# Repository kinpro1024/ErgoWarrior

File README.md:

# ErgoWarrior

**ErgoWarrior is a completely open-source, ergonomic hitbox-style leverless controller. It was born out of a complete lack of contoured open-source ergonomic hitbox designs.**

*To the best of my knowledge, this is the **first open-source** Contoured Ergonomic Hitbox on a public platform.*

# Major Update: An overhaul of the Handle/Bridge Design is in the works. (Released as v1.1.0)

**I had the Handle Fail and Break in my flight luggage as it was being thrown around. ErgoWarrior was designed to be robust, and this result was not good enough. The overhaul will also address the inability to completely remove cables once assembled, enhancing repairability.**

**ErgoWarrior v1.1.0 Mechanical Design.**

**ErgoWarrior v1.0.0 Mechanical Design.**

**ErgoWarrior v1.0.0 has a robust handle. (It did not, that has been fixed.)**

**Right Half of ErgoWarrior's Pre-Alpha Build.**

## Why an Ergo-Design Matters

Traditional flat controllers force the wrists and fingers into unnatural positions. Over time, this can lead to discomfort, fatigue, and even injuries such as Repetitive Strain Injury (RSI) or Carpal Tunnel Syndrome.

An ergo-design, **like ErgoWarrior**, is built to keep your hands and wrists in a natural, relaxed posture. This brings several benefits:

- **Reduced Strain and Injury Risk**: Many people (myself included) are highly prone to wrist injuries, ErgoWarrior is designed to keep wrists neutral, lowering stress on muscles and tendons.
- **Better Comfort for Extended Use**: Less fatigue during long sessions.
- **Improved Precision and Performance**: Inputs are always in reach and yet equally intuitive.
- **Natural Hand Posture**: Designed to closely match human anatomy for optimal control and comfort.
- **Advanced Techniques Still Possible**: Techniques like double taps or quick buffering inputs are still very much preserved and possible.

In short, ergonomic designs are not just about comfort, they improve performance and intend to protect your hands over the long term.

### Hardware and Assembly

Raspberry Pi Pico is the main dev-board platform for ErgoWarrior. May change to a custom dev-board in the future.

Cherry MX Low Profile switches are the switches used throughtout all forseen generations of Ergowarrior.

ErgoWarrior is designed to go with [M3 Hex Socket 10mm Screws](https://onlyscrews.in/products/m3-x-10mm-hex-allen-socket-head-high-tensile12-9-black-anodized-screw?_pos=17&_sid=9edb84e19&_ss=r) and [8mm M3 Injection Molding Brass Inserts](https://onlyscrews.in/products/m3-x-8mm-brass-threaded-inserts).

Refer to Instructions.md for full instructions in assembly.

**Print Settings:** All Prints except the ultralight arcade button are done at 0.2mm layer height with the latter at 0.08mm LH. Refer to 3mf files for full details.
**Note:** Some Sanding is required on the jump buttons for optimal fit.

### Firmware

Firmware used for ErgoWarrior is a tweaked build of [GP2040-CE](https://github.com/OpenStickCommunity/GP2040-CE). Plug-and-Play firmware will drop soon. Until then stock GP2040-CE for the Raspberry Pi Pico must be used. Keybinds as below:

## Note on Sizing

The ErgoWarrior is currently available in **only one size**, which corresponds to my personal hand size.  
If you need a different size, you may scale and modify the model yourself with the step files to better fit your requirements.

*If you're unsure how to do that, feel free to open an issue thread in the repository. I’m not making any promises at the moment, but I will look into it if possible.*

## Timeline

### v0.0.0 and v0.5.0 (Alpha and Beta Builds) (Released on 19/Oct/2025) (Deprecated)

A kof style 4+4 (L+R) controller was released as Alpha Build by mid-October ~~with a beta build arriving on the same platform in late October~~. (Alpha Build out.) (Beta build cancelled, changes merged with v1.)

### v1.0.0 (Full Release) (Released on 29/Nov/2025) (Deprecated)

A Third-Strike style controller with a (6+10)* (L+R) layout was slated for release in ~~mid-November~~ late-November (Delay in arrival of PCBs).

### v1.1.0 (Released on 20/Apr/2026)

This was not a a release I had planned, however as the ErgoWarrior handle failed in what I would call abnormal but expected load conditions, I have completely reworked the handle, this time using Topology Optimisation to make it absolutely sure it does not fail like that again.

\* **Tentative, may change.**

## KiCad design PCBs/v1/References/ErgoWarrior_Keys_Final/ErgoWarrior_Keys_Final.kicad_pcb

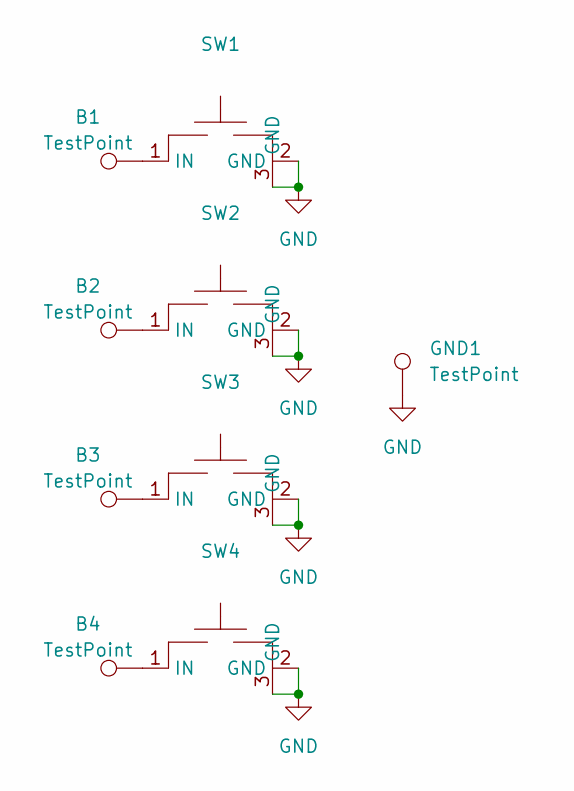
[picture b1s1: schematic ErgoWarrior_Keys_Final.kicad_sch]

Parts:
B1, B2, B3, B4: TestPoint; TestPoint_THTPad_D1.5mm_Drill0.7mm
GND1: TestPoint; TestPoint_THTPad_1.5x1.5mm_Drill0.7mm
SW1, SW2, SW3, SW4: Cherry_MX_LP_Mirrorable

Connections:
GND: GND1.1, SW1.2 (GND), SW1.3 (GND), SW2.2 (GND), SW2.3 (GND), SW3.2 (GND), SW3.3 (GND), SW4.2 (GND), SW4.3 (GND)
unnamed: B1.1, SW1.1 (IN)
unnamed: B2.1, SW2.1 (IN)
unnamed: B3.1, SW3.1 (IN)
unnamed: B4.1, SW4.1 (IN)

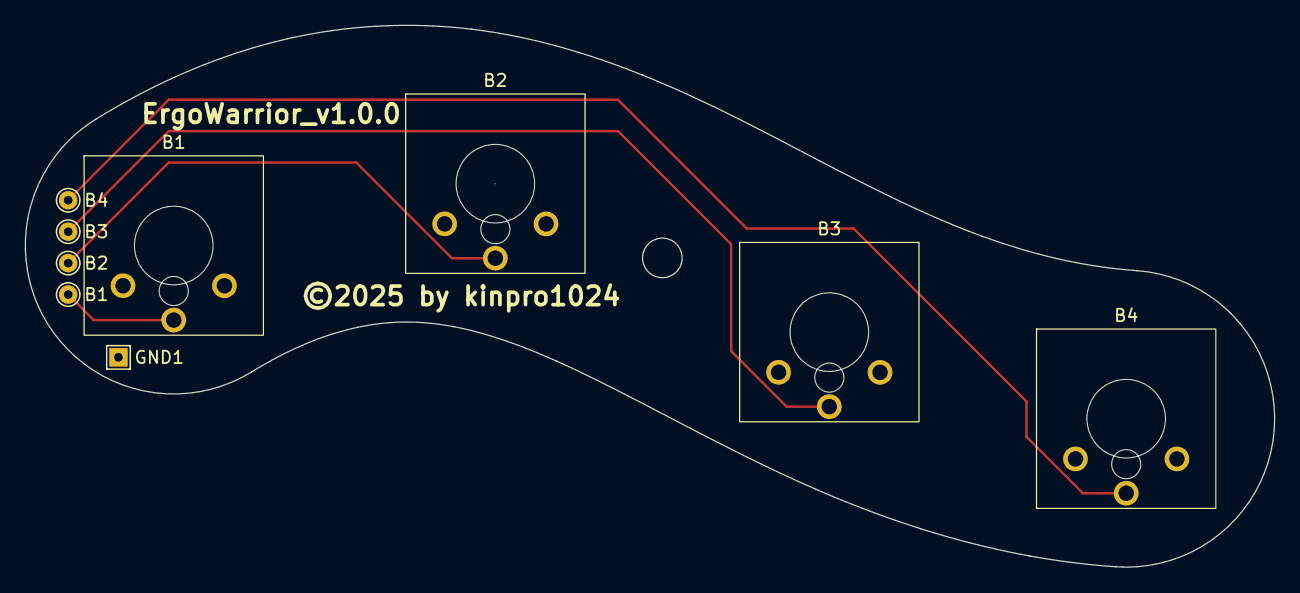
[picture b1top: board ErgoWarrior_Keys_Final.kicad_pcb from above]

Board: 2 copper layers, 101.0 x 43.8 mm, 9 parts (0 on the bottom side), 5 nets.

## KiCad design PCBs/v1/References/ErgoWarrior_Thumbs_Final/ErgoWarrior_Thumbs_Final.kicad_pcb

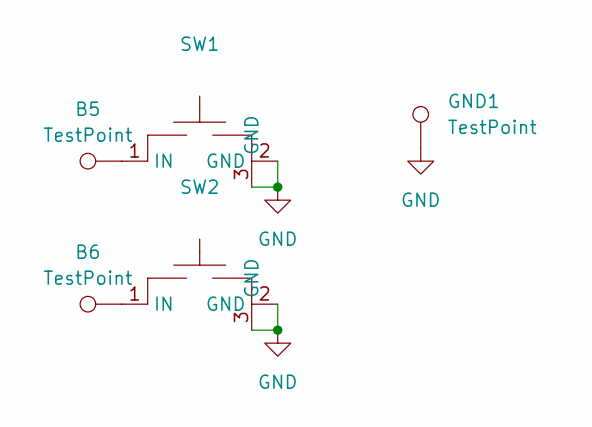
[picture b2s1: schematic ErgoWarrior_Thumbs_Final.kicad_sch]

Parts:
B5, B6: TestPoint; TestPoint_THTPad_D1.5mm_Drill0.7mm
GND1: TestPoint; TestPoint_THTPad_1.5x1.5mm_Drill0.7mm
SW1, SW2: Cherry_MX_LP_Mirrorable

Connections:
GND: GND1.1, SW1.2 (GND), SW1.3 (GND), SW2.2 (GND), SW2.3 (GND)
unnamed: B5.1, SW1.1 (IN)
unnamed: B6.1, SW2.1 (IN)

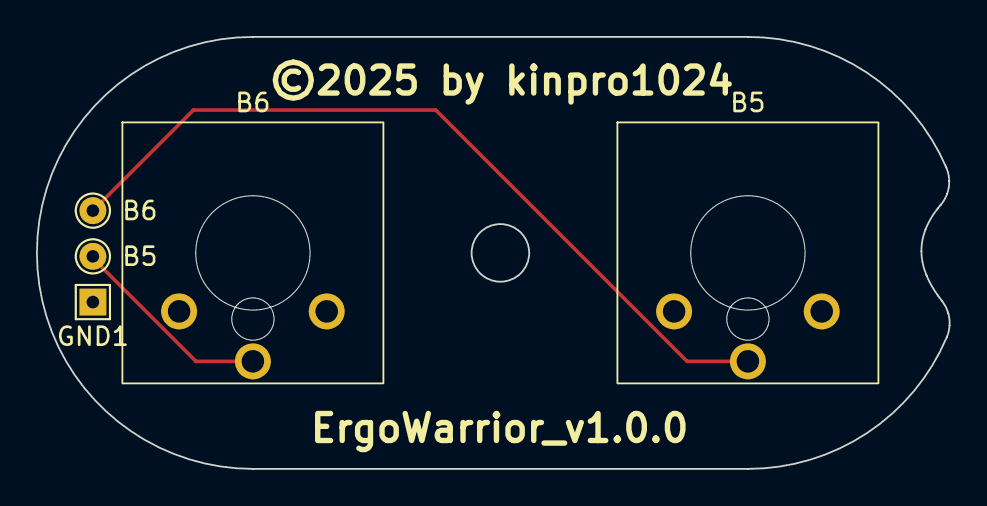
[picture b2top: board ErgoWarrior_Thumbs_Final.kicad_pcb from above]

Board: 2 copper layers, 50.7 x 24.0 mm, 5 parts (0 on the bottom side), 3 nets.

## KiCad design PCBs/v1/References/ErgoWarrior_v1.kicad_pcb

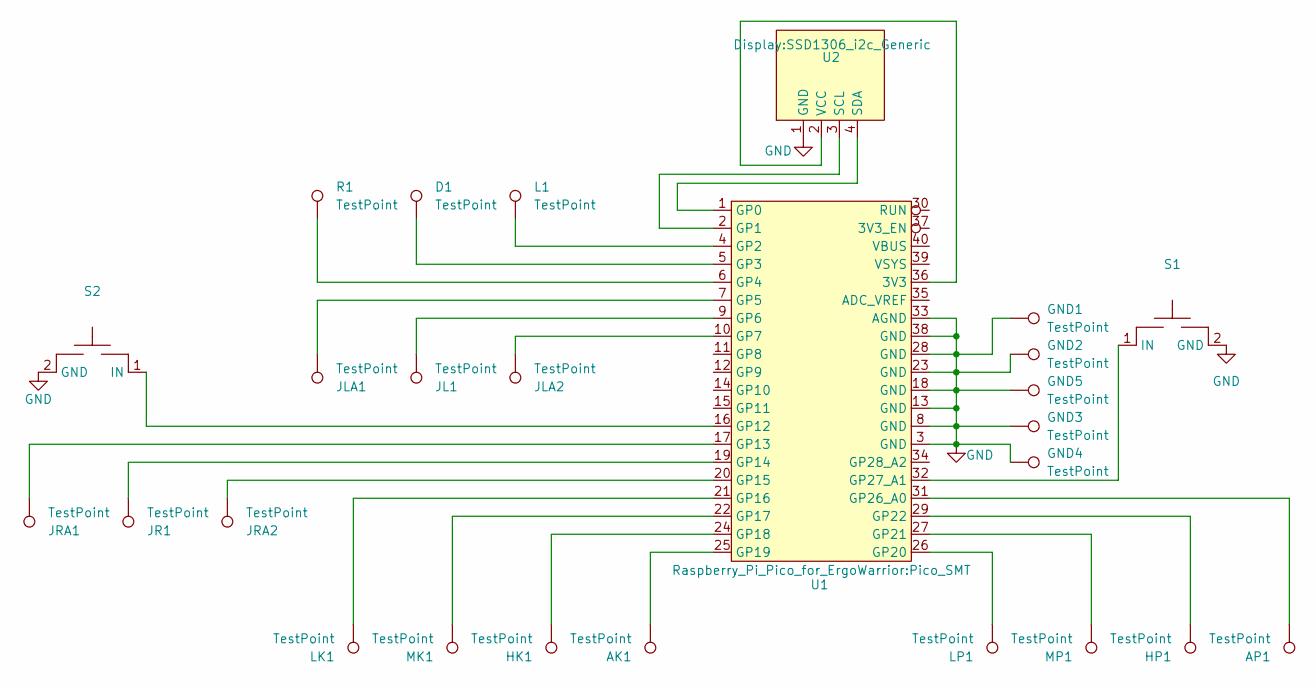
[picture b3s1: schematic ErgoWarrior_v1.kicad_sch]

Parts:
AK1: TestPoint; TestPoint_Pad_D2.0mm
AP1: TestPoint; TestPoint_Pad_D2.0mm
D1: TestPoint; TestPoint_Pad_D2.0mm
GND1, GND2, GND3, GND4, GND5: TestPoint; TestPoint_Pad_D2.0mm
HK1: TestPoint; TestPoint_Pad_D2.0mm
HP1: TestPoint; TestPoint_Pad_D2.0mm
JL1: TestPoint; TestPoint_Pad_D2.0mm
JLA1, JLA2: TestPoint; TestPoint_Pad_D2.0mm
JR1: TestPoint; TestPoint_Pad_D2.0mm
JRA1, JRA2: TestPoint; TestPoint_Pad_D2.0mm
L1: TestPoint; TestPoint_Pad_D2.0mm
LK1: TestPoint; TestPoint_Pad_D2.0mm
LP1: TestPoint; TestPoint_Pad_D2.0mm
MK1: TestPoint; TestPoint_Pad_D2.0mm
MP1: TestPoint; TestPoint_Pad_D2.0mm
R1: TestPoint; TestPoint_Pad_D2.0mm
S1, S2: Cherry_MX_LP
U1: Pico_SMT
U2: SSD1306_i2c_Generic

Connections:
GND: GND1.1, GND2.1, GND3.1, GND4.1, GND5.1, S1.2 (GND), S2.2 (GND), U1.3 (GND), U1.8 (GND), U1.13 (GND), U1.18 (GND), U1.23 (GND), U1.28 (GND), U1.33 (AGND), U1.38 (GND), U2.1 (GND)
unnamed: S1.1 (IN), U1.32 (GP27_A1)
unnamed: S2.1 (IN), U1.16 (GP12)
unnamed: U1.36 (3V3), U2.2 (VCC)
unnamed: U1.1 (GP0), U2.4 (SDA)
unnamed: U1.2 (GP1), U2.3 (SCL)
unnamed: L1.1, U1.4 (GP2)
unnamed: D1.1, U1.5 (GP3)
unnamed: R1.1, U1.6 (GP4)
unnamed: JLA1.1, U1.7 (GP5)
unnamed: JL1.1, U1.9 (GP6)
unnamed: JLA2.1, U1.10 (GP7)
unnamed: JRA1.1, U1.17 (GP13)
unnamed: JR1.1, U1.19 (GP14)
unnamed: JRA2.1, U1.20 (GP15)
unnamed: LK1.1, U1.21 (GP16)
unnamed: MK1.1, U1.22 (GP17)
unnamed: HK1.1, U1.24 (GP18)
unnamed: AK1.1, U1.25 (GP19)
unnamed: LP1.1, U1.26 (GP20)
unnamed: MP1.1, U1.27 (GP21)
unnamed: HP1.1, U1.29 (GP22)
unnamed: AP1.1, U1.31 (GP26_A0)

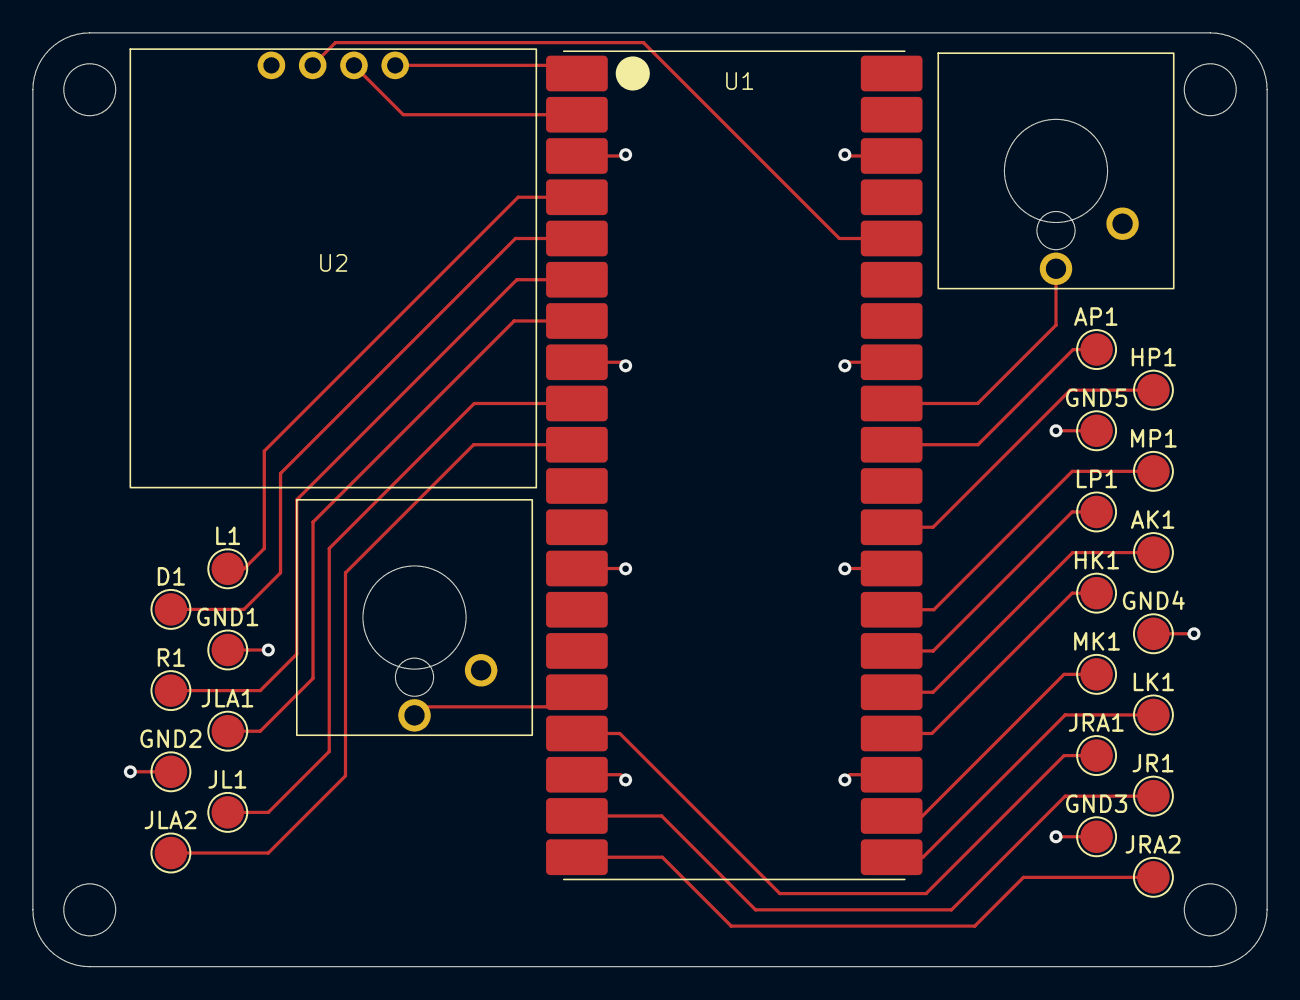
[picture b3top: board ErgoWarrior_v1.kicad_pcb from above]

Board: 2 copper layers, 76.0 x 57.5 mm, 26 parts (0 on the bottom side), 23 nets.

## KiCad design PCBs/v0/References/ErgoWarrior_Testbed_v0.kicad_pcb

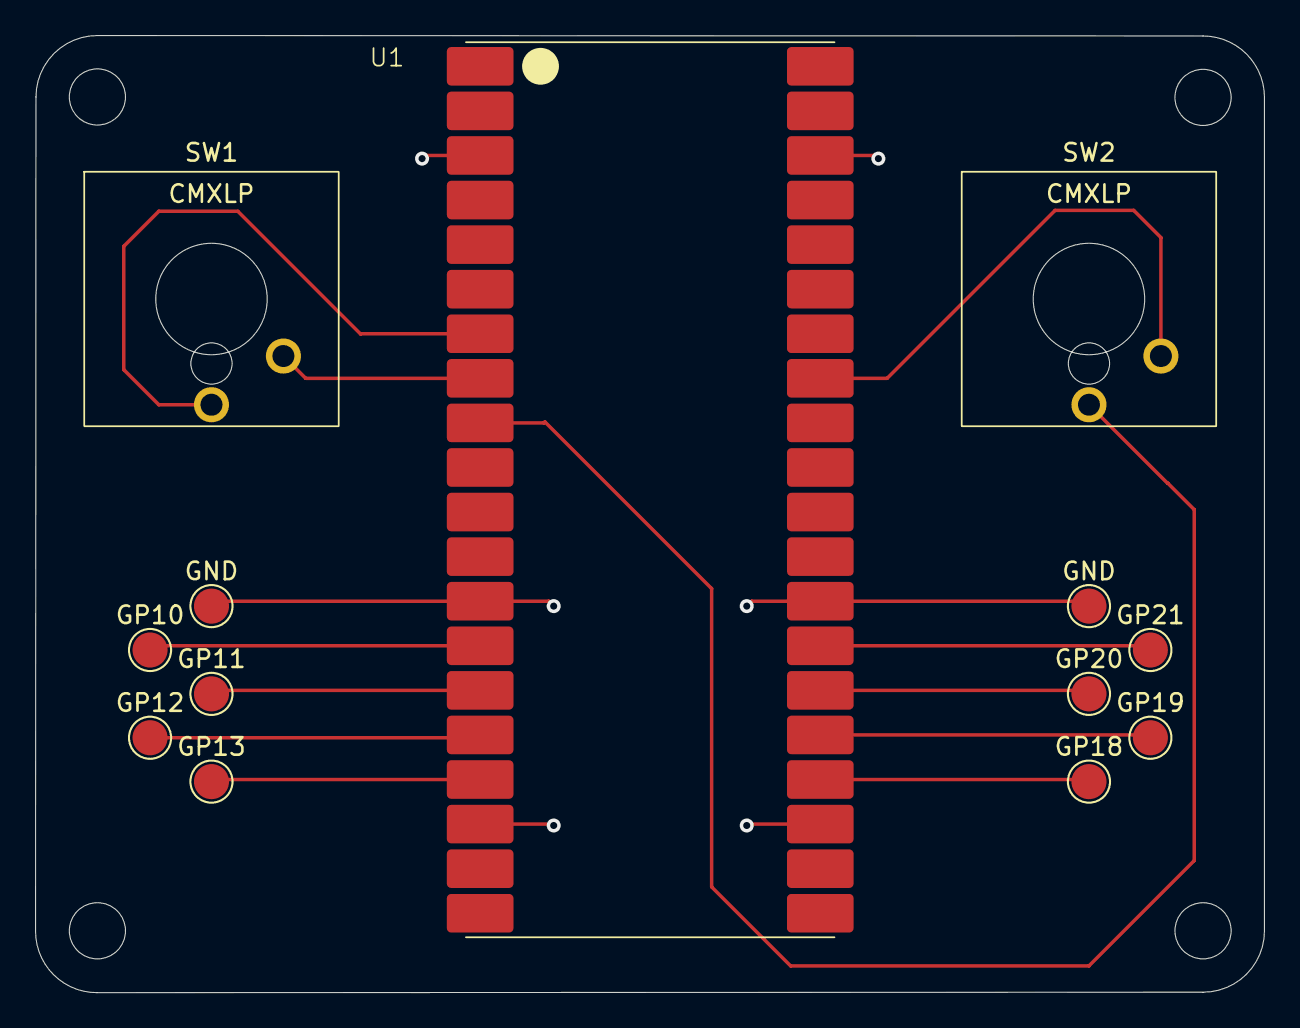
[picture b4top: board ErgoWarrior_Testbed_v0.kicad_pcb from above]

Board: 2 copper layers, 70.0 x 54.5 mm, 13 parts (0 on the bottom side), 11 nets.

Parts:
GND: TestPoint; TestPoint_Pad_D2.0mm
GND#2: TestPoint; TestPoint_Pad_D2.0mm
GP10, GP11, GP12, GP13, GP18, GP19, GP20, GP21: TestPoint; TestPoint_Pad_D2.0mm
SW1, SW2: CMXLP; Cherry_MX_LP
U1: PICO; Pico_SMT

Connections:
GND: GND.1, GND#2.1, SW1.2 (GND), SW2.2 (GND), U1.3 (GND), U1.8 (GND), U1.13 (GND), U1.18 (GND), U1.23 (GND), U1.28 (GND), U1.33 (AGND), U1.38 (GND)
unnamed: SW1.1 (IN), U1.7 (GP5)
unnamed: SW2.1 (IN), U1.9 (GP6)
unnamed: GP10.1, U1.14 (GP10)
unnamed: GP11.1, U1.15 (GP11)
unnamed: GP12.1, U1.16 (GP12)
unnamed: GP13.1, U1.17 (GP13)
unnamed: GP18.1, U1.24 (GP18)
unnamed: GP19.1, U1.25 (GP19)
unnamed: GP20.1, U1.26 (GP20)
unnamed: GP21.1, U1.27 (GP21)

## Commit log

2025-09-28 Initial commit - added filesystem and README.
2025-09-28 Fixed image path in README.
2025-09-28 Added 3D_files which are WIP.
2025-09-28 added KiCad v0 gerbers and references.
2025-09-28 added KiCad v1 references.
2025-09-28 Added STEP Files.
2025-09-30 Added STL files for Ultralight Button and Caddy.
2025-09-30 Remove .DS_Store and add .gitignore to ignore it
2025-10-01 Added thumb caddy for v0.
2025-10-02 added bridge STL files.
2025-10-12 Updated Readme.md with New Updates.
2025-10-12 Added all v1 reference PCB files.
2025-10-12 Added LFS tracking for STL files.
2025-10-12 Add Git LFS rule for *.stl
2025-10-12 cleanup after lfs
2025-10-12 Added final 3d files for alpha build
2025-10-13 Added finalised designs for v1.0.0
2025-10-19 Added final v0_alpha fixes.
2025-10-19 v0_alpha release.
2025-10-28 Updated README.md with revised timeline.
2025-11-15 Updated v1 Release Date.
2025-11-15 v1.0.0 Mechanical Design Revealed.
2025-11-22 Added Final v1 Design Images.
2025-11-29 v1.0.0 Release Pushed
2025-11-30 Instructions for assembly and STEP files for scaling.
2026-01-26 Update Announcement.
2026-04-01 v1.1.0 announcement
2026-04-20 v1.1.0 commit
2026-04-20 v1.1.0 instructions update
2026-04-20 v1.1.0 README update

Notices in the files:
PCBs/v1/References/ErgoWarrior_Keys_Final/ErgoWarrior_Keys_Final.kicad_pcb:
©2025 by kinpro1024
